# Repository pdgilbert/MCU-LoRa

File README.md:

# MCU-LoRa

Combine an MCU and LoRa radio onto a castellated PCB board.

##  Status: Prototype.

## Summary

Kicad project WIP.

The `.png` files are produced from kicad  in the `3D Viewer`  with `File > Export Current View as PNG`.

## History

 - Version 0.1.0 WIP circa 2025-09.

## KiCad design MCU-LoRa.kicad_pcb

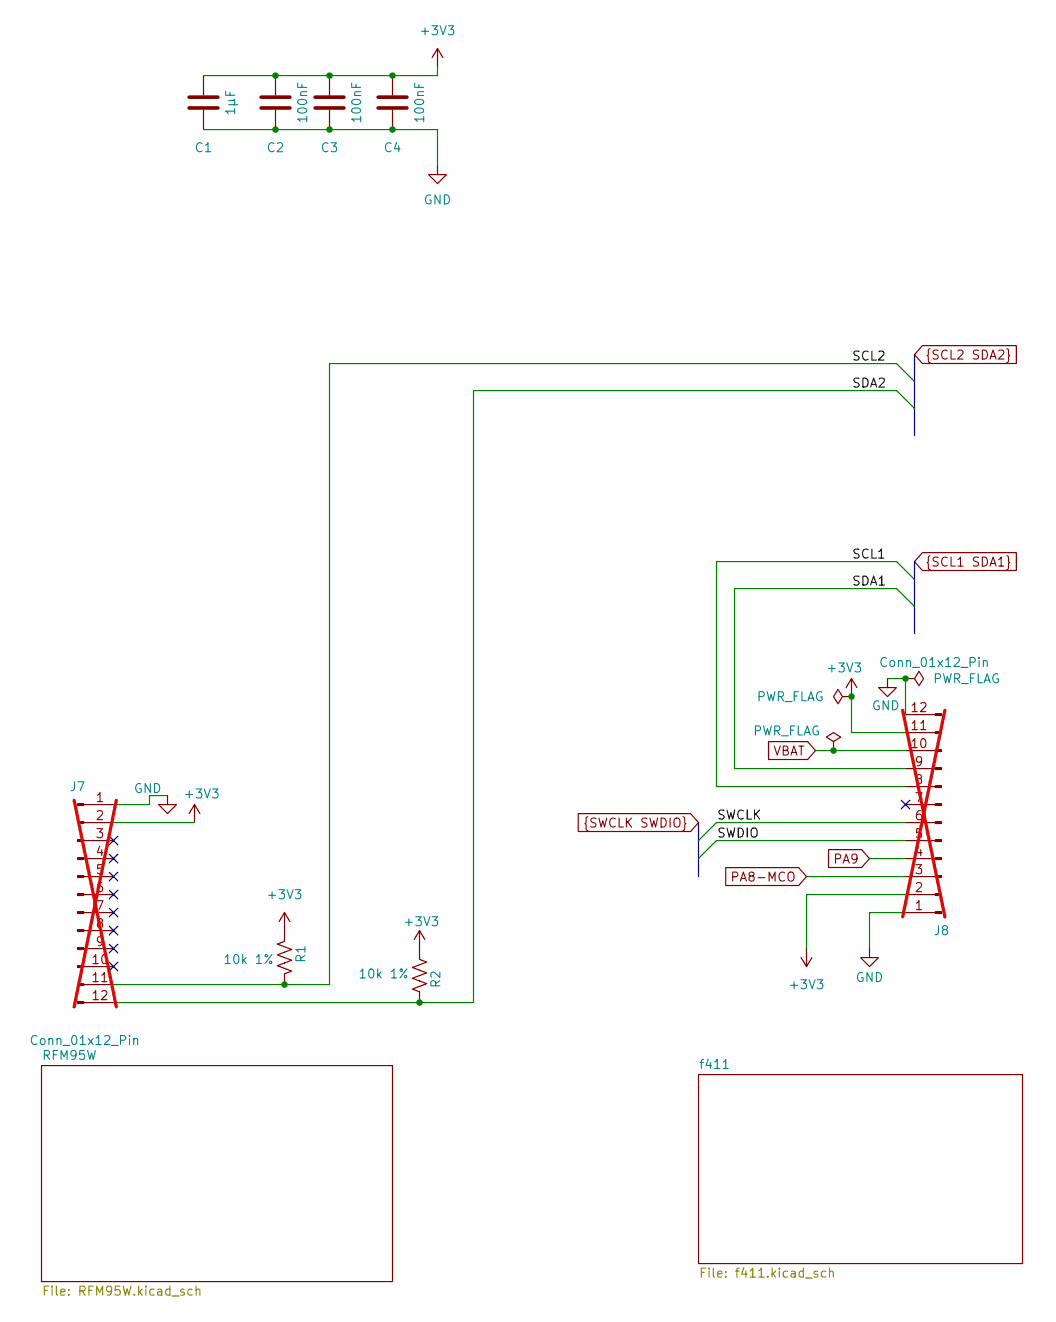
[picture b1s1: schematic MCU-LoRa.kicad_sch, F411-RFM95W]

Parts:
C1: 1µF; C_0402_1005Metric
C2, C3, C4: 100nF; C_0402_1005Metric
J7, J8: Conn_01x12_Pin; Castellated_Header_1x12_P2.00mm_Vertical; not fitted
R1, R2: 10k 1%; R_0402_1005Metric

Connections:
+3V3: C1.1, C2.1, C3.1, C4.1, J7.2, J8.2, J8.11, R1.1, R2.2; also elsewhere on the board
GND: C1.2, C2.2, C3.2, C4.2, J7.1, J8.1, J8.12; also elsewhere on the board
PA8-MCO: J8.3; also elsewhere on the board
PA9: J8.4; also elsewhere on the board
SCL1: J8.8; also elsewhere on the board
SCL2: J7.11, R1.2; also elsewhere on the board
SDA1: J8.9; also elsewhere on the board
SDA2: J7.12, R2.1; also elsewhere on the board
SWCLK: J8.6; also elsewhere on the board
SWDIO: J8.5; also elsewhere on the board
VBAT: J8.10; also elsewhere on the board

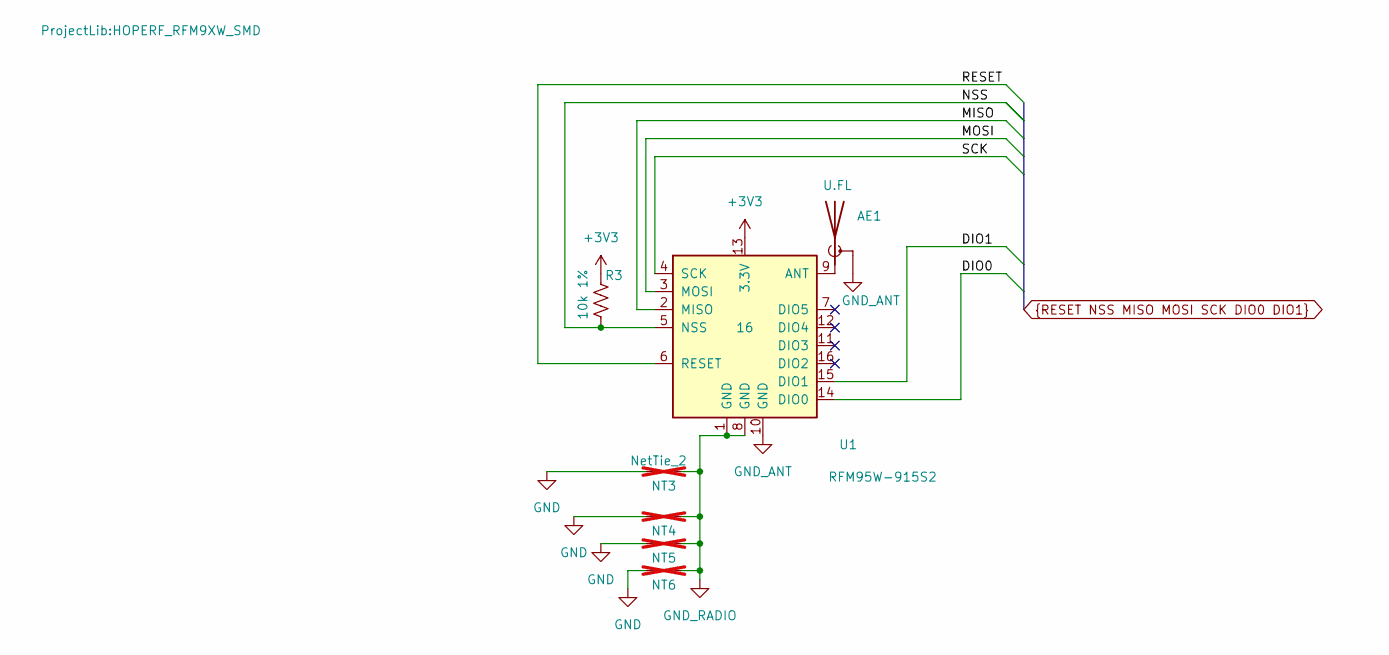
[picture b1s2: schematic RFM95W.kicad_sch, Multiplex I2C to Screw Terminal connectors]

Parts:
AE1: U.FL; U.FL_Molex_MCRF_73412-0110_Vertical; MfgPart U.FL-R-SMT-1
NT3, NT4, NT5, NT6: NetTie_2; NetTie-2_SMD_Pad0.5mm; not fitted
R3: 10k 1%; R_0402_1005Metric
U1: RFM95W-915S2; HOPERF_RFM9XW_SMD; MfgPart RFM95W-915S2

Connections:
+3V3: R3.1, U1.13 (3.3V); also elsewhere on the board
DIO0: U1.14 (DIO0); also elsewhere on the board
DIO1: U1.15 (DIO1); also elsewhere on the board
GND: NT3.1, NT4.1, NT5.1, NT6.1; also elsewhere on the board
GND_ANT: AE1.2 (Shield), U1.10 (GND)
GND_RADIO: NT3.2, NT4.2, NT5.2, NT6.2, U1.1 (GND), U1.8 (GND)
MISO: U1.2 (MISO); also elsewhere on the board
MOSI: U1.3 (MOSI); also elsewhere on the board
NSS: R3.2, U1.5 (NSS); also elsewhere on the board
unnamed: AE1.1 (A), U1.9 (ANT)
RESET: U1.6 (RESET); also elsewhere on the board
SCK: U1.4 (SCK); also elsewhere on the board

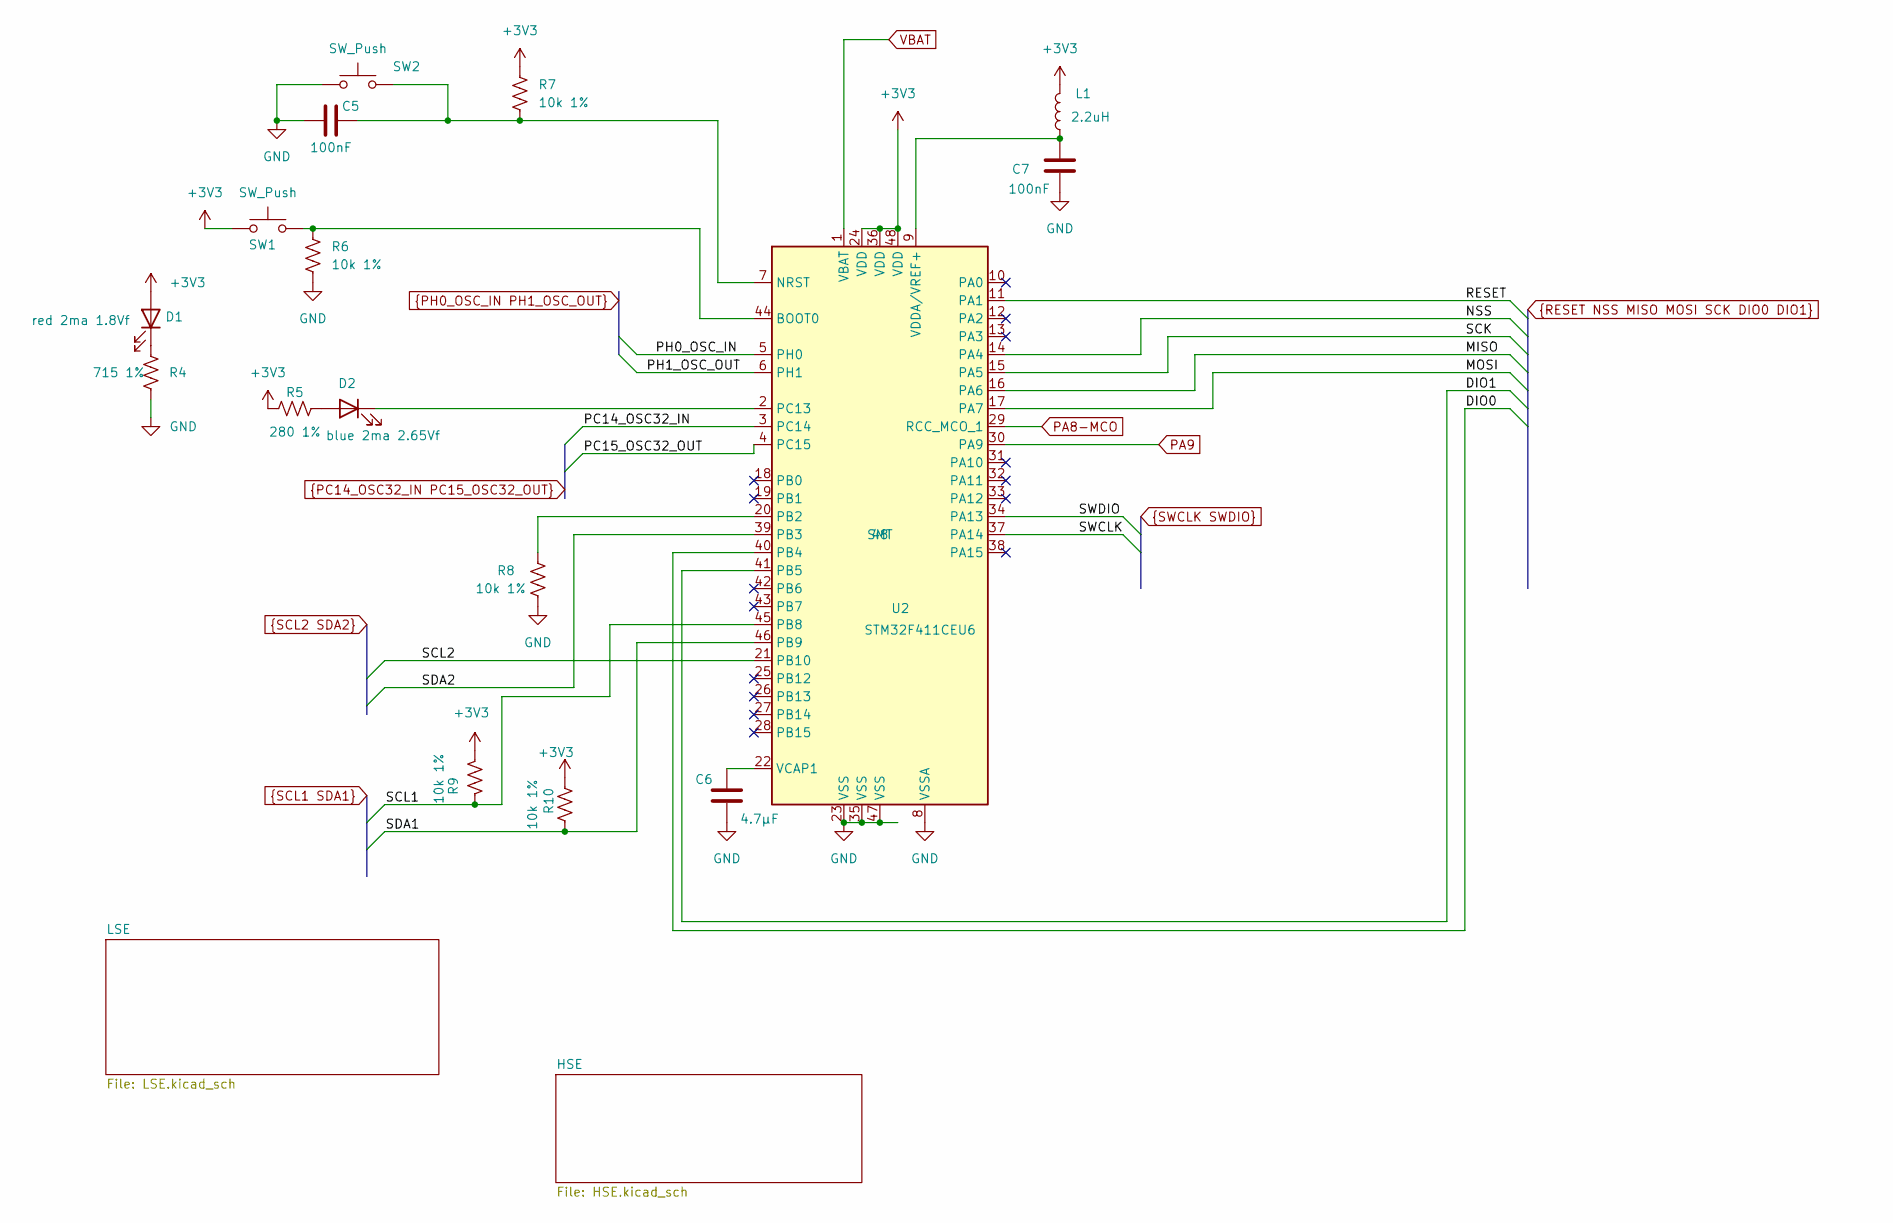
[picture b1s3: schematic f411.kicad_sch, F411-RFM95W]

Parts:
C5, C7: 100nF; C_0402_1005Metric
C6: 4.7µF; C_0402_1005Metric
D1: red 2ma 1.8Vf; LED_0603_1608Metric; MfgPart APT1608LSECK/J3-PRV
D2: blue 2ma 2.65Vf; LED_0603_1608Metric; MfgPart APT1608LVBC/D
L1: 2.2uH; L_0402_1005Metric; MfgPart MLZ1005M2R2WT000
R4: 715 1%; R_0402_1005Metric
R5: 280 1%; R_0402_1005Metric
R6, R7, R8, R9, R10: 10k 1%; R_0402_1005Metric
SW1, SW2: SW_Push; SW_SPST_B3U-1000P; MfgPart B3U-1000P
U2: STM32F411CEU6; QFN-48-1EP_7x7mm_P0.5mm_EP5.6x5.6mm; MfgPart STM32F411CEU6

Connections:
+3V3: D1.2 (A), L1.2, R5.1, R7.1, R9.1, R10.1, SW1.1, U2.24 (VDD), U2.36 (VDD), U2.48 (VDD); also elsewhere on the board
DIO0: U2.40 (PB4); also elsewhere on the board
DIO1: U2.41 (PB5); also elsewhere on the board
GND: C5.1, C6.2, C7.2, R4.2, R6.2, R8.2, SW2.1, U2.8 (VSSA), U2.23 (VSS), U2.35 (VSS), U2.47 (VSS), U2.49 (VSS); also elsewhere on the board
MISO: U2.16 (PA6); also elsewhere on the board
MOSI: U2.17 (PA7); also elsewhere on the board
NSS: U2.14 (PA4); also elsewhere on the board
unnamed: D1.1 (K), R4.1
unnamed: D2.2 (A), R5.2
unnamed: D2.1 (K), U2.2 (PC13)
unnamed: R6.1, SW1.2, U2.44 (BOOT0)
unnamed: C5.2, R7.2, SW2.2, U2.7 (NRST)
unnamed: R8.1, U2.20 (PB2)
unnamed: C6.1, U2.22 (VCAP1)
unnamed: C7.1, L1.1, U2.9 (VDDA/VREF+)
PA8-MCO: U2.29 (RCC_MCO_1); also elsewhere on the board
PA9: U2.30 (PA9); also elsewhere on the board
PC14_OSC32_IN: U2.3 (PC14); also elsewhere on the board
PC15_OSC32_OUT: U2.4 (PC15); also elsewhere on the board
PH0_OSC_IN: U2.5 (PH0); also elsewhere on the board
PH1_OSC_OUT: U2.6 (PH1); also elsewhere on the board
RESET: U2.11 (PA1); also elsewhere on the board
SCK: U2.15 (PA5); also elsewhere on the board
SCL1: R9.2, U2.45 (PB8); also elsewhere on the board
SCL2: U2.21 (PB10); also elsewhere on the board
SDA1: R10.2, U2.46 (PB9); also elsewhere on the board
SDA2: U2.39 (PB3); also elsewhere on the board
SWCLK: U2.37 (PA14); also elsewhere on the board
SWDIO: U2.34 (PA13); also elsewhere on the board
VBAT: U2.1 (VBAT); also elsewhere on the board

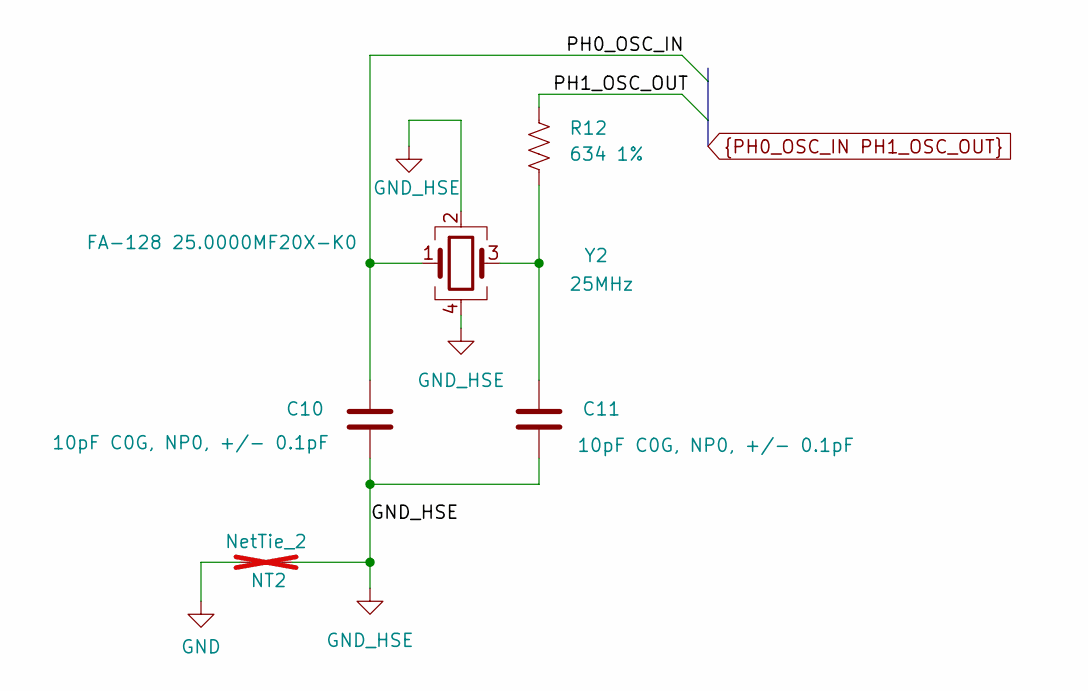
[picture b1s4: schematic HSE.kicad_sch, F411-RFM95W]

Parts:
C10, C11: 10pF C0G, NP0, +/- 0.1pF; C_0402_1005Metric
NT2: NetTie_2; NetTie-2_SMD_Pad0.5mm; not fitted
R12: 634 1%; R_0402_1005Metric
Y2: 25MHz; Crystal_SMD_2016-4Pin_2.0x1.6mm; MfgPart FA-128 25.0000MF20X-K0

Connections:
GND: NT2.1; also elsewhere on the board
GND_HSE: C10.1, C11.1, NT2.2, Y2.2, Y2.4
unnamed: C11.2, R12.2, Y2.3
PH0_OSC_IN: C10.2, Y2.1; also elsewhere on the board
PH1_OSC_OUT: R12.1; also elsewhere on the board

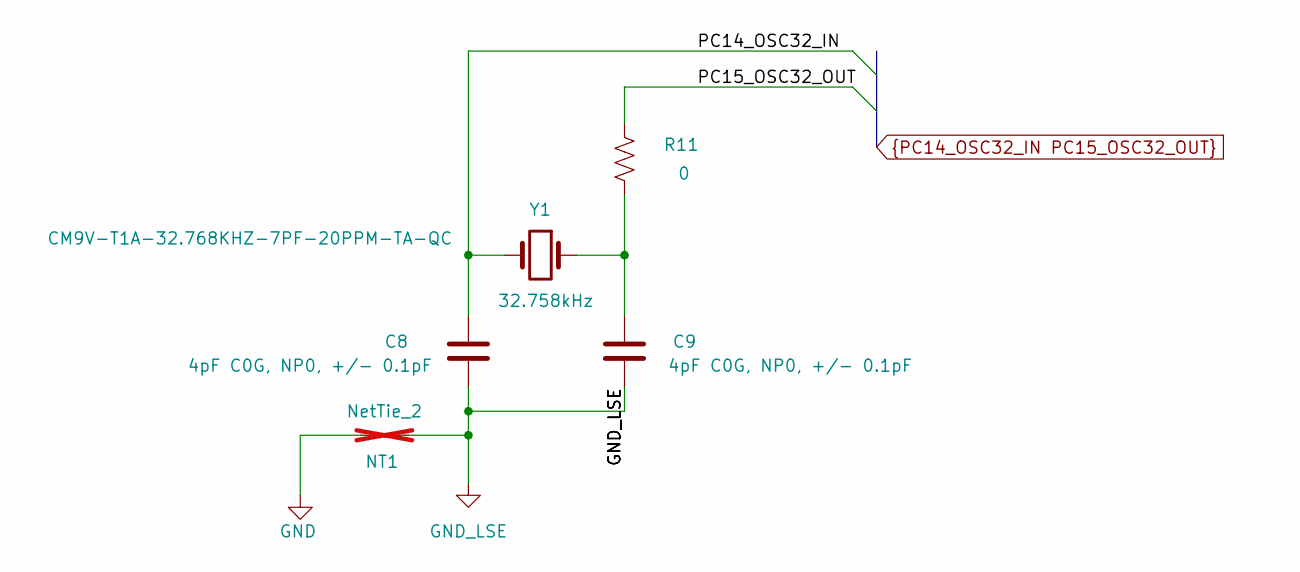
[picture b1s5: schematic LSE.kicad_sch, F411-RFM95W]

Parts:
C8, C9: 4pF C0G, NP0, +/- 0.1pF; C_0402_1005Metric
NT1: NetTie_2; NetTie-2_SMD_Pad0.5mm; not fitted
R11: 0; R_0402_1005Metric
Y1: 32.758kHz; Crystal_SMD_MicroCrystal_CM9V-T1A-2Pin_1.6x1.0mm; MfgPart CM9V-T1A-32.768KHZ-7PF-20PPM-TA-QC

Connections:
GND: NT1.1; also elsewhere on the board
GND_LSE: C8.1, C9.1, NT1.2
unnamed: C9.2, R11.2, Y1.1
PC14_OSC32_IN: C8.2, Y1.2; also elsewhere on the board
PC15_OSC32_OUT: R11.1; also elsewhere on the board

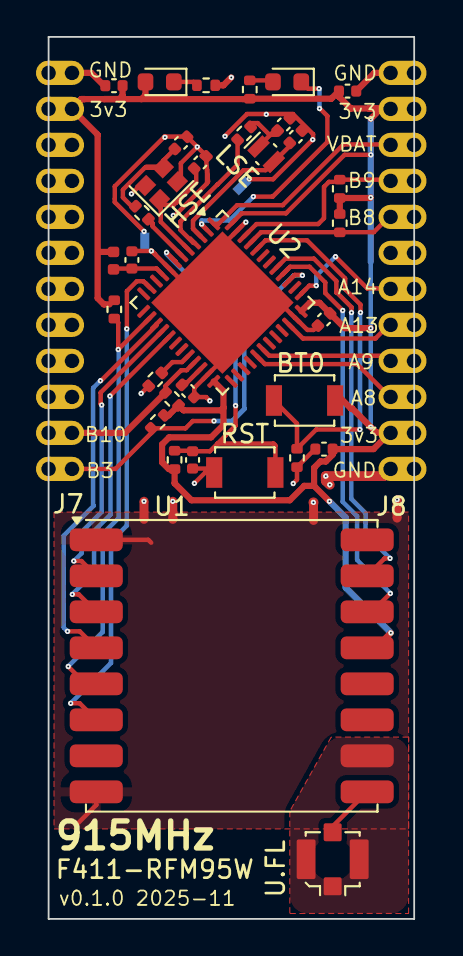
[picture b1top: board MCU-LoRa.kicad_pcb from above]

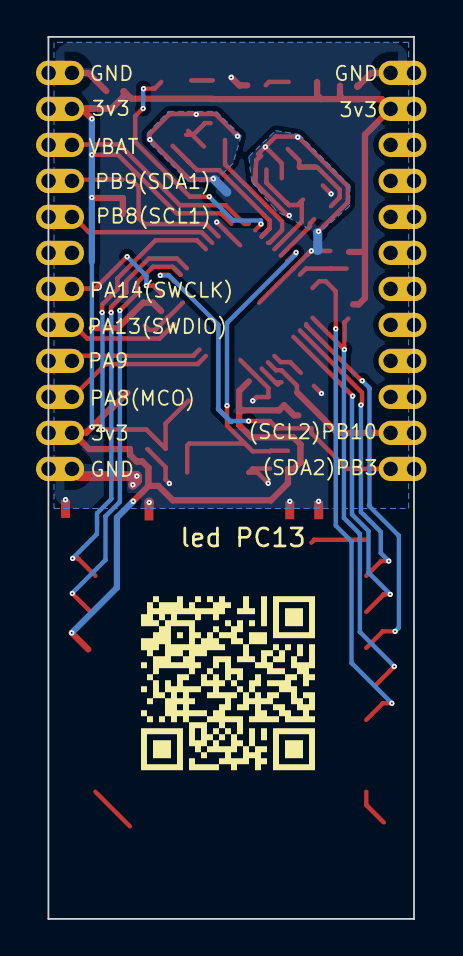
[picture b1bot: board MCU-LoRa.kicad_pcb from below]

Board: 2 copper layers, 20.3 x 49.0 mm, 41 parts (2 on the bottom side), 37 nets.

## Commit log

2025-09-12 initial commit. F411-RFM95W ERC good. DRC has lots of warnings and much cleanup needed.
2025-09-12 gitignore adjustment
2025-09-12 changed from vias to microvias. ERC ok. DRC has only warnings related to castellated edges cutting footprints.
2025-09-17 3v3 trace moved to back side.
2025-09-17 move antenna U.FL closer to corner.
2025-09-23 ongoing
2025-09-27 MCU moved down closer to radio. Connectors need better arrangement.
2025-09-30 ongoing cleanup. DRC clean excluding edge cut of castellated holes.
2025-11-10 reduced with of board.
2025-11-11 added QR code
2025-11-17 settled on 24-pins. Fairly clean castillated pin header but no footprint yet. Decided against rotating radio.
2025-11-17 minor cleanup.
2025-11-18 cleanup. ERC and DRC good. No footprint yet.
2025-11-27 added footprint and step model. Cleaned up silkscreen and fab layers.
